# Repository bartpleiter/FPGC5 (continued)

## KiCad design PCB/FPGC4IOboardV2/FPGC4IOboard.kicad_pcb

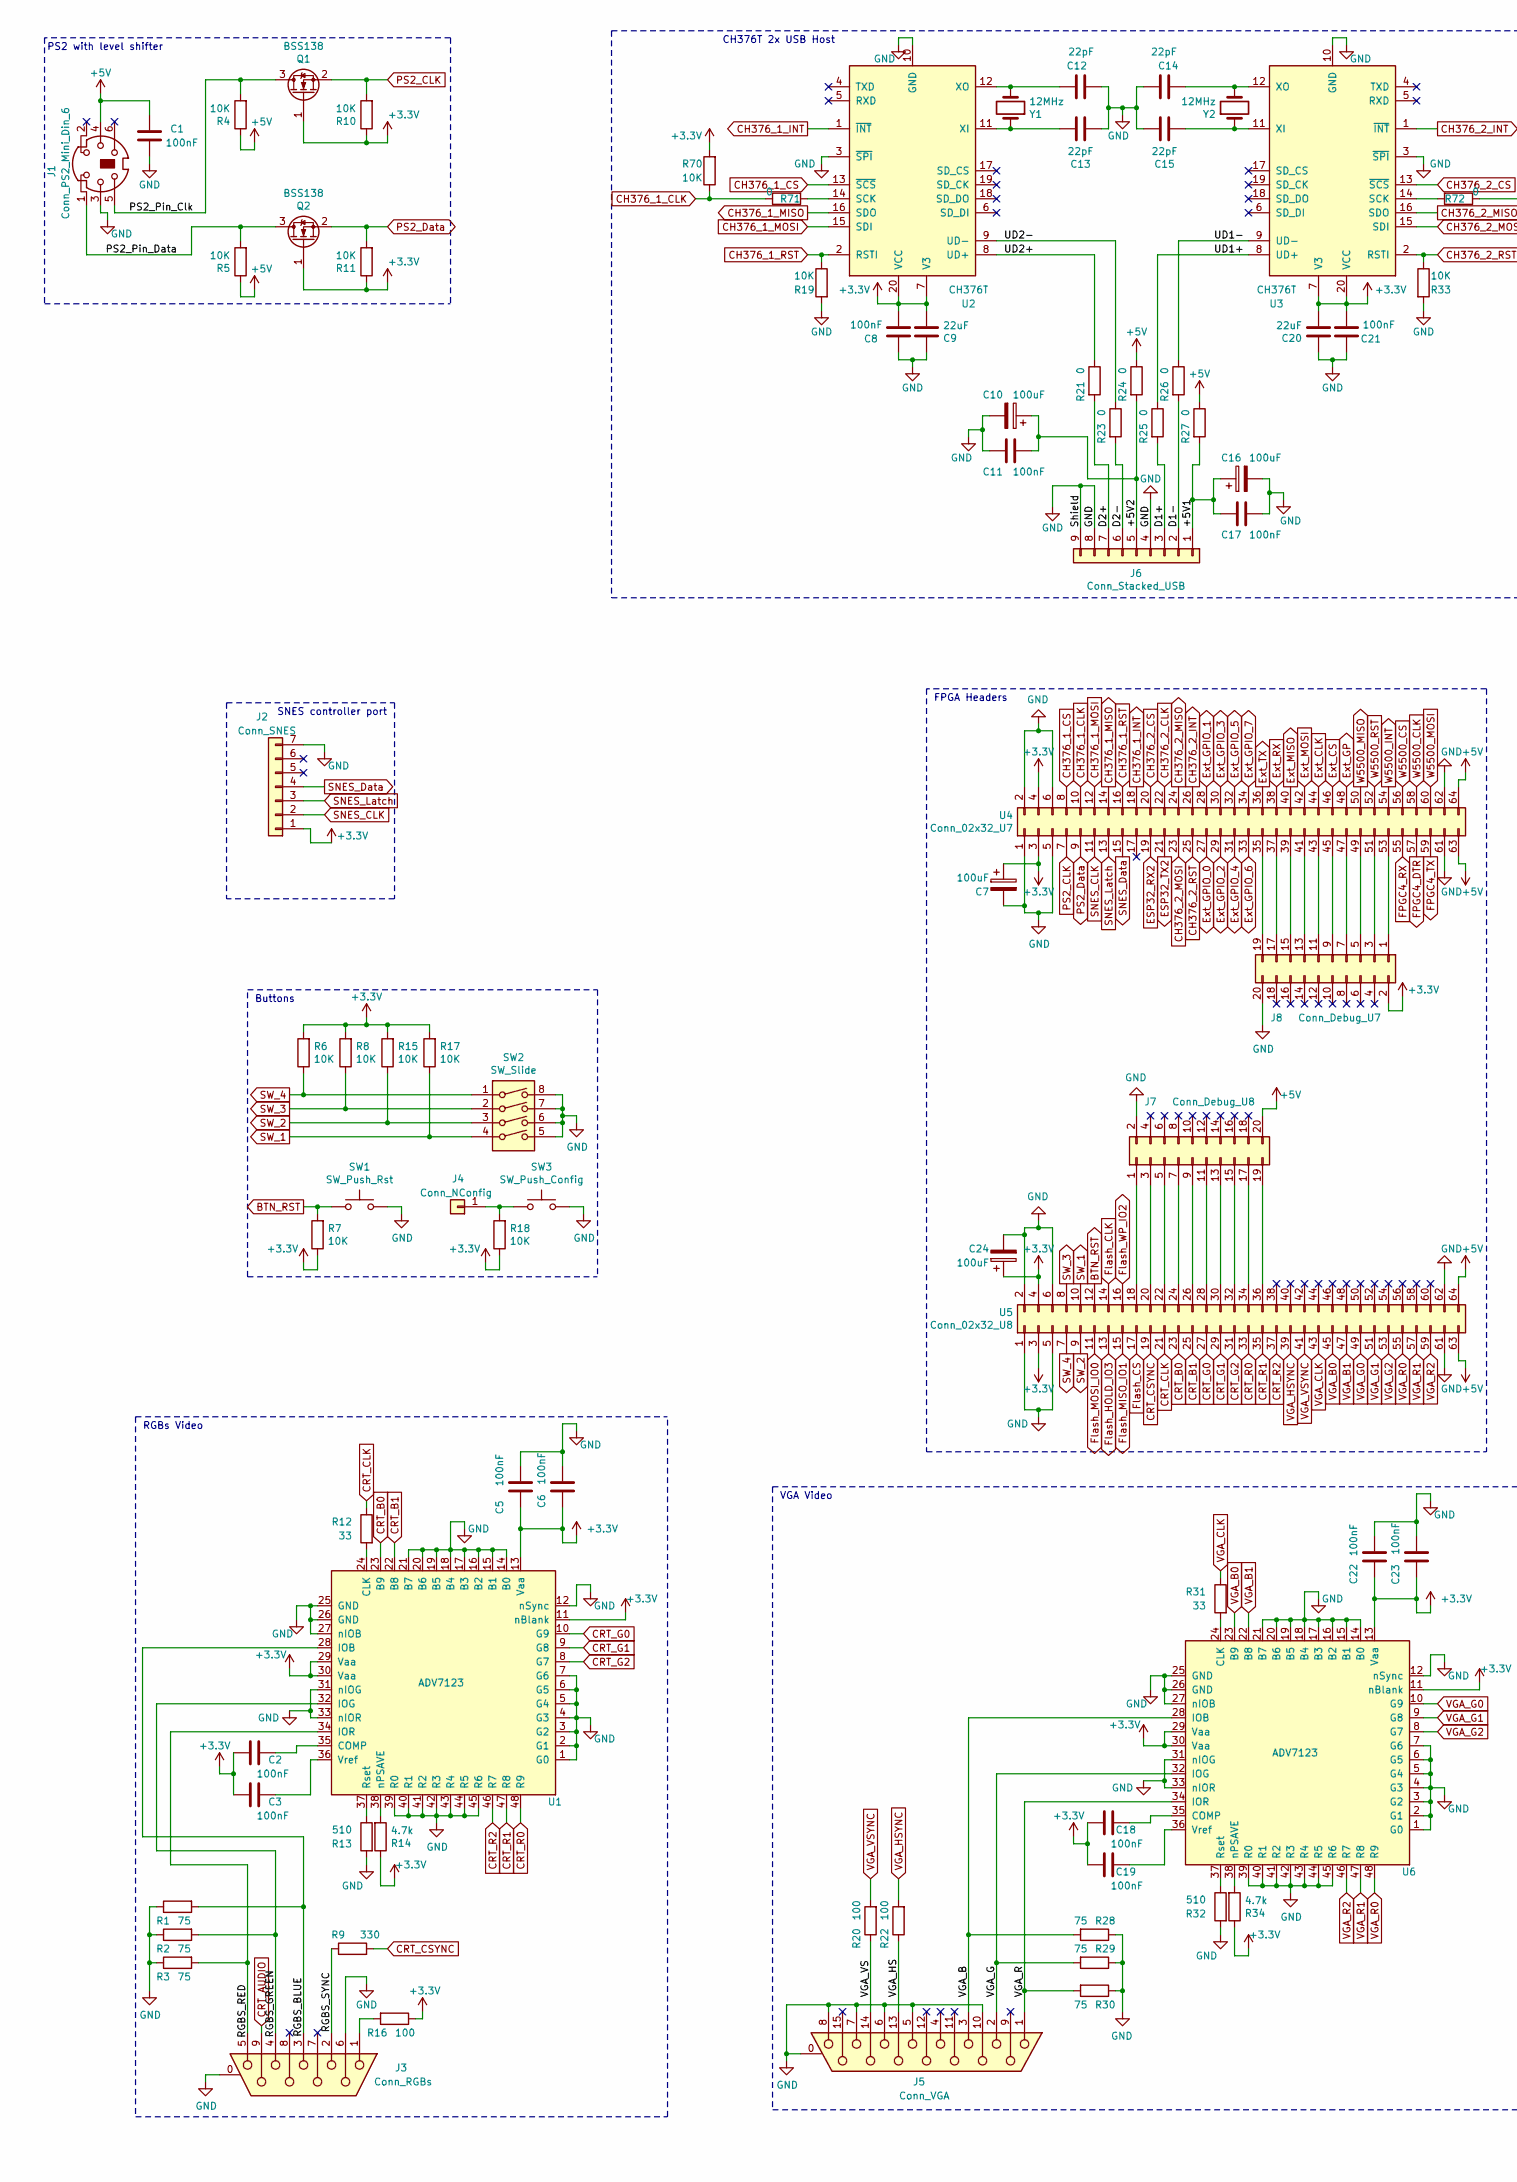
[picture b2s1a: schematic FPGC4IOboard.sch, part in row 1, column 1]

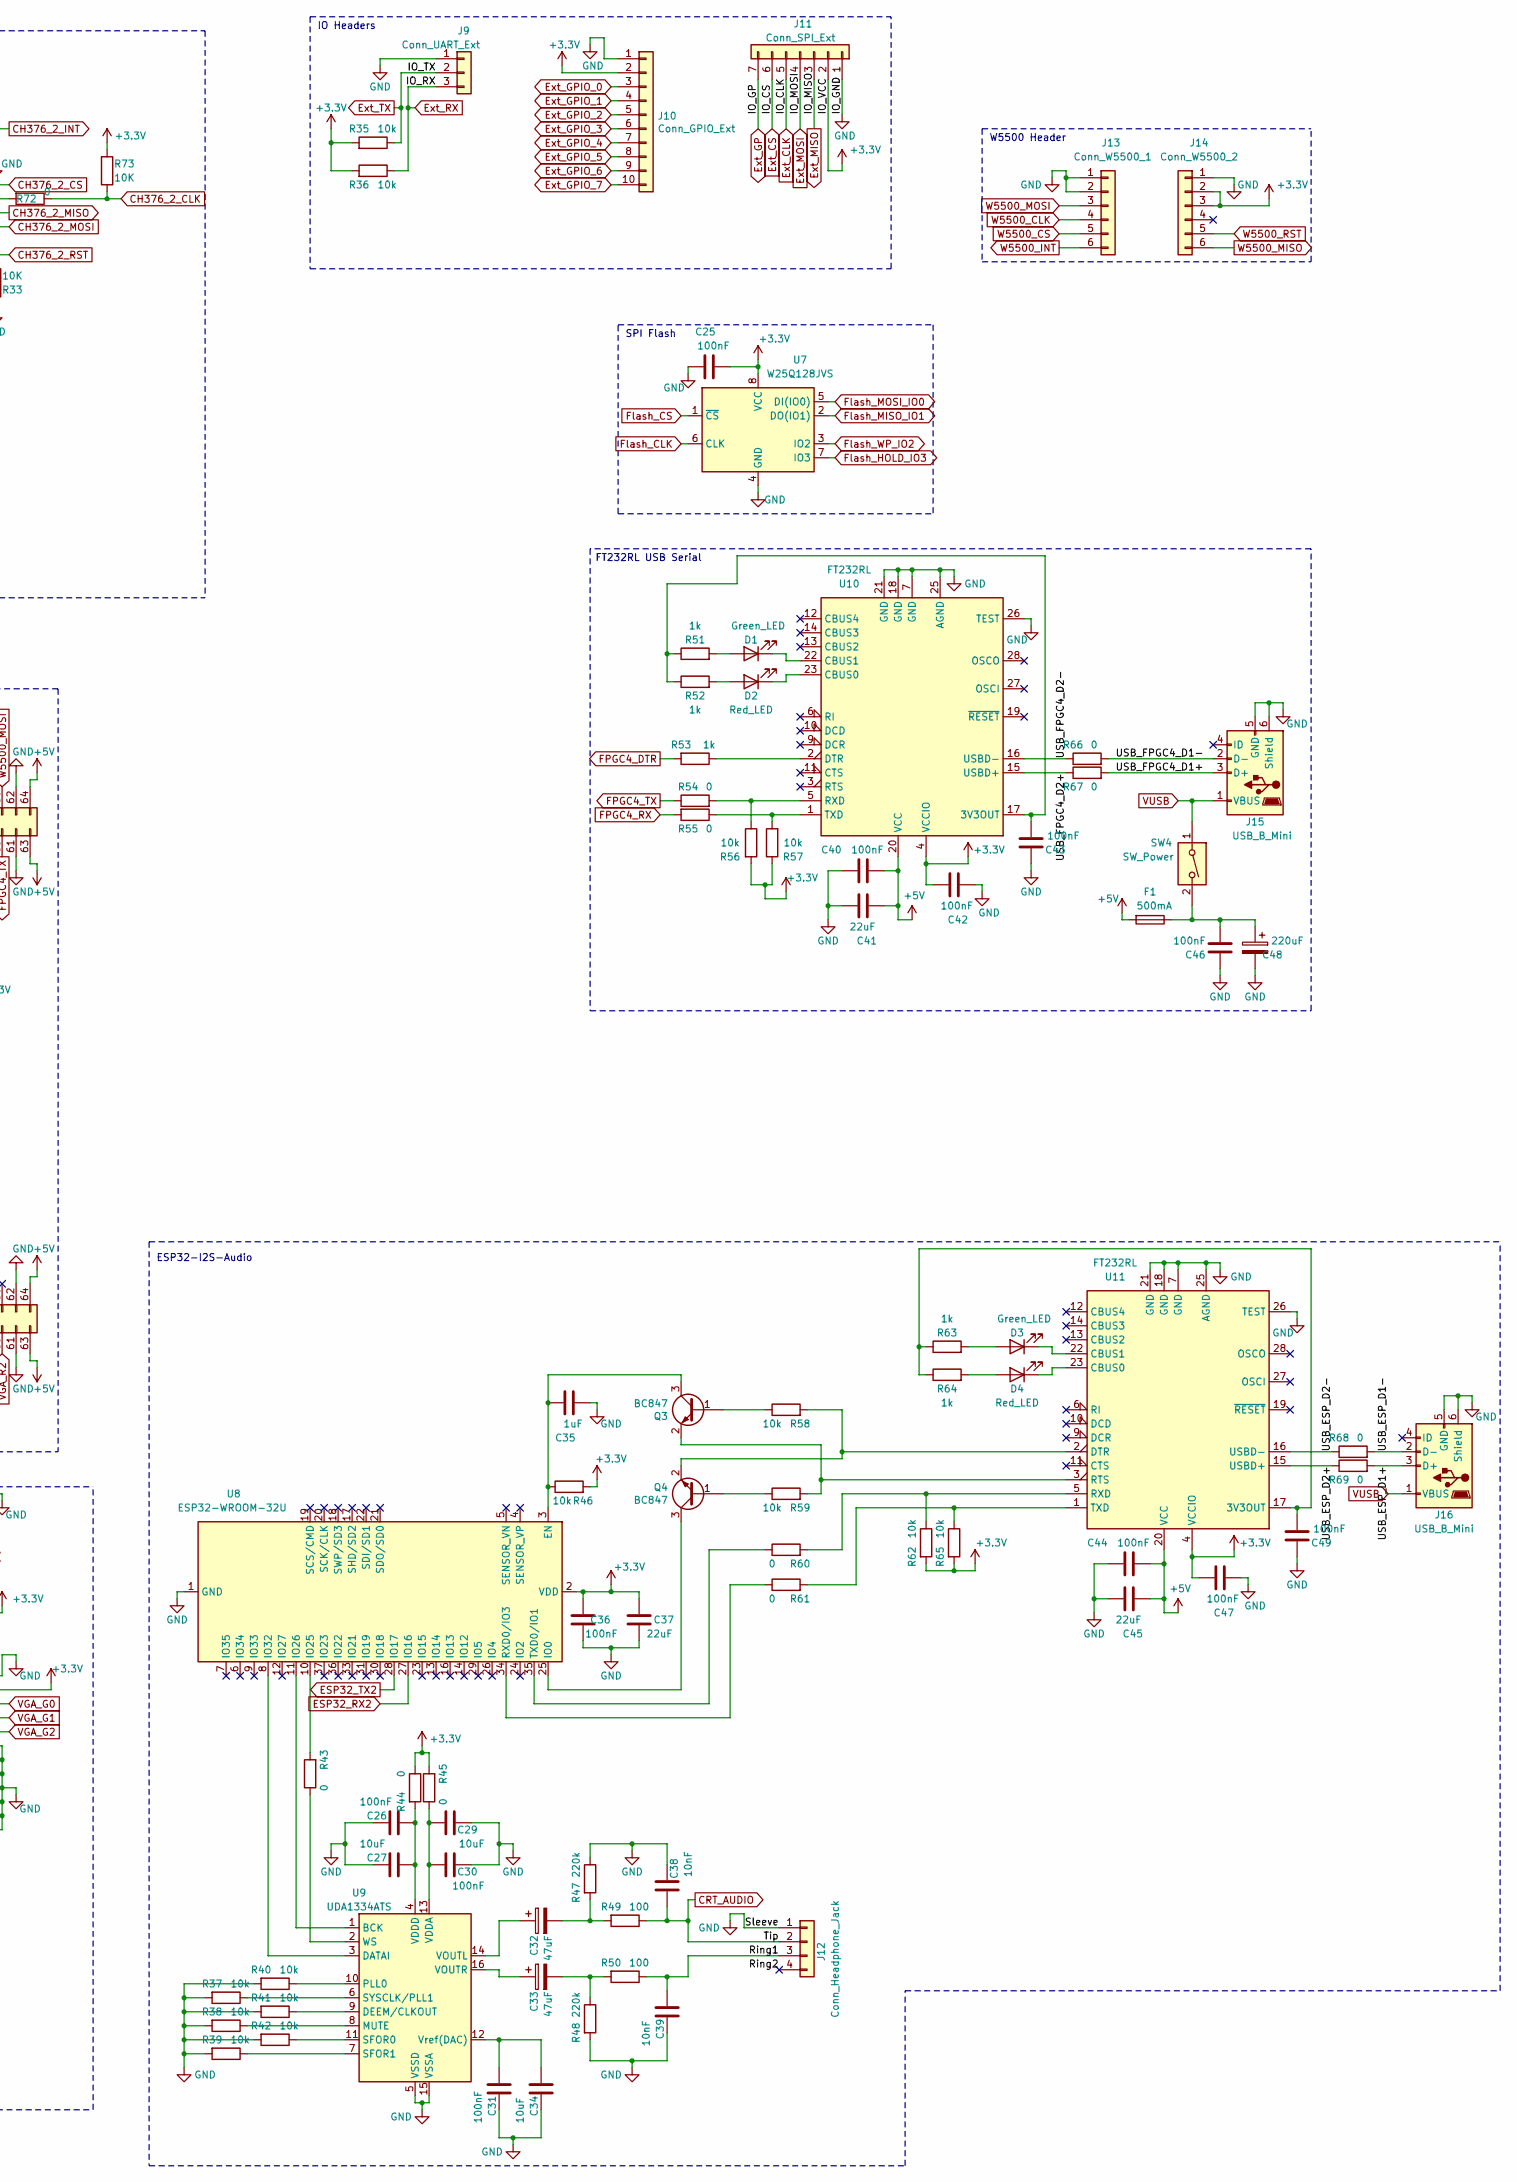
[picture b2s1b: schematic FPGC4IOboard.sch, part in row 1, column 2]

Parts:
C1, C2, C3, C5, C6, C8, C11, C17, C18, C19, C21, C22, C23, C25, C26, C30, C31, C36, C40, C42, C43, C44, C46, C47, C49: 100nF; C_0805_2012Metric_Pad1.15x1.40mm_HandSolder
C7, C10, C16, C24: 100uF; CP_Radial_D4.0mm_P2.00mm
C9, C20, C37, C41, C45: 22uF; C_0805_2012Metric_Pad1.15x1.40mm_HandSolder
C12, C13, C14, C15: 22pF; C_0805_2012Metric_Pad1.15x1.40mm_HandSolder
C27, C29, C34: 10uF; C_0805_2012Metric_Pad1.15x1.40mm_HandSolder
C32, C33: 47uF; CP_Radial_D4.0mm_P2.00mm
C35: 1uF; C_0805_2012Metric_Pad1.15x1.40mm_HandSolder
C38, C39: 10nF; C_0805_2012Metric_Pad1.15x1.40mm_HandSolder
C48: 220uF; CP_Radial_D5.0mm_P2.00mm
D1, D3: Green_LED; LED_0805_2012Metric_Pad1.15x1.40mm_HandSolder
D2, D4: Red_LED; LED_0805_2012Metric_Pad1.15x1.40mm_HandSolder
F1: 500mA; Fuse_1812_4532Metric_Pad1.30x3.40mm_HandSolder
J1: Conn_PS2_Mini_Din_6; Connector_Mini-DIN_Female_6Pin_2rows
J2: Conn_SNES; SNES_controller_port
J3: Conn_RGBs; DSUB9_CRT
J4: Conn_NConfig; PinHeader_1x01_P2.54mm_Vertical
J5: Conn_VGA; VGA_EDAC
J6: Conn_Stacked_USB; USB_A_Wuerth_61400826021_Horizontal_Stacked
J7: Conn_Debug_U8; PinHeader_2x10_P2.54mm_Vertical
J8: Conn_Debug_U7; PinHeader_2x10_P2.54mm_Vertical
J9: Conn_UART_Ext; PinSocket_1x03_P2.54mm_Vertical
J10: Conn_GPIO_Ext; PinSocket_1x10_P2.54mm_Vertical
J11: Conn_SPI_Ext; PinSocket_1x07_P2.54mm_Vertical
J12: Conn_Headphone_Jack; TRRS-PJ-320A
J13: Conn_W5500_1; PinSocket_1x06_P2.54mm_Vertical
J14: Conn_W5500_2; PinSocket_1x06_P2.54mm_Vertical
J15, J16: USB_B_Mini; USB_Mini-B_Lumberg_2486_01_Horizontal
Q1, Q2: BSS138; SOT-23
Q3, Q4: BC847; SOT-23
R1, R2, R3, R28, R29, R30: 75; R_0805_2012Metric_Pad1.15x1.40mm_HandSolder
R4, R5, R6, R7, R8, R10, R11, R15, R17, R18, R19, R33, R70, R73: 10K; R_0805_2012Metric_Pad1.15x1.40mm_HandSolder
R9: 330; R_0805_2012Metric_Pad1.15x1.40mm_HandSolder
R12, R31: 33; R_0805_2012Metric_Pad1.15x1.40mm_HandSolder
R13, R32: 510; R_0805_2012Metric_Pad1.15x1.40mm_HandSolder
R14, R34: 4.7k; R_0805_2012Metric_Pad1.15x1.40mm_HandSolder
R16, R20, R22, R49, R50: 100; R_0805_2012Metric_Pad1.15x1.40mm_HandSolder
R21, R23, R24, R25, R26, R27, R43, R44, R45, R54, R55, R60, R61, R66, R67, R68, R69, R71, R72: 0; R_0805_2012Metric_Pad1.15x1.40mm_HandSolder
R35, R36, R37, R38, R39, R40, R41, R42, R46, R56, R57, R58, R59, R62, R65: 10k; R_0805_2012Metric_Pad1.15x1.40mm_HandSolder
R47, R48: 220k; R_0805_2012Metric_Pad1.15x1.40mm_HandSolder
R51, R52, R53, R63, R64: 1k; R_0805_2012Metric_Pad1.15x1.40mm_HandSolder
SW1: SW_Push_Rst; SW_Tactile_SPST_Angled_PTS645Vx39-2LFS
SW2: SW_Slide; SW_DIP_SPSTx04_Slide_6.7x11.72mm_W8.61mm_P2.54mm_LowProfile
SW3: SW_Push_Config; SW_Tactile_SPST_Angled_PTS645Vx39-2LFS
SW4: SW_Power; switchAngled
U1, U6: ADV7123; LQFP-48_7x7mm_P0.5mm
U2, U3: CH376T; SSOP-20_5.3x7.2mm_P0.65mm
U4: Conn_02x32_U7; PinHeader_2x32_P2.54mm_Vertical
U5: Conn_02x32_U8; PinHeader_2x32_P2.54mm_Vertical
U7: W25Q128JVS; SOIC-8_5.23x5.23mm_P1.27mm
U8: ESP32-WROOM-32U
U9: UDA1334ATS; SSOP-16_4.4x5.2mm_P0.65mm
U10, U11: FT232RL; SSOP-28_5.3x10.2mm_P0.65mm
Y1, Y2: 12MHz; Crystal_HC49-4H_Vertical

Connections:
+3V3: C2.1, C3.1, C5.2, C6.1, C7.1, C8.2, C9.2, C18.1, C19.1, C20.2, C21.2, C22.2, C23.1, C24.1, C25.2, C36.2, C37.2, C42.2, C47.2, J2.1, J8.2, J10.2, J11.2, J14.2, J14.3, Q1.1 (G), Q2.1 (G), R6.2, R7.1, R8.2, R10.1, R11.1, R14.1, R15.2, R16.1, R17.2, R18.1, R34.1, R35.2, R36.2, R44.1, R45.2, R46.2, R56.2, R57.1, R62.2, R65.2, R70.2, R73.2, U1.11 (nBlank), U1.13 (Vaa), U1.29 (Vaa), U1.30 (Vaa), U2.7 (V3), U2.20 (VCC), U3.7 (V3), U3.20 (VCC), U4.3, U4.4, U5.3, U5.4, U6.11 (nBlank), U6.13 (Vaa), U6.29 (Vaa), U6.30 (Vaa), U7.8 (VCC), U8.2 (VDD), U10.4 (VCCIO), U11.4 (VCCIO)
+5V: C1.1, C40.2, C41.1, C44.2, C45.1, F1.2, J1.4, J7.20, R4.1, R5.1, R24.1, R27.1, U4.63, U4.64, U5.63, U5.64, U10.20 (VCC), U11.20 (VCC)
/+5V1: C16.1, C17.2, J6.1, R27.2
/+5V2: C10.1, C11.2, J6.5, R24.2
/D1+: J6.3, R25.2
/D1-: J6.2, R26.2
/D2+: J6.7, R21.2
/D2-: J6.6, R23.2
/PS2_Pin_Clk: J1.5, Q1.3 (D), R4.2
/PS2_Pin_Data: J1.1, Q2.3 (D), R5.2
/RGBS_BLUE: J3.3, R1.2, U1.28 (IOB)
/RGBS_GREEN: J3.4, R2.2, U1.32 (IOG)
/RGBS_RED: J3.5, R3.2, U1.34 (IOR)
/RGBS_SYNC: J3.2, R9.1
/Ring1: C39.1, J12.3, R50.1
/Ring2: J12.4
/UD1+: R25.1, U3.8 (UD+)
/UD1-: R26.1, U3.9 (UD-)
/UD2+: R21.1, U2.8 (UD+)
/UD2-: R23.1, U2.9 (UD-)
/USB_ESP_D1+: J16.3 (D+), R69.2
/USB_ESP_D1-: J16.2 (D-), R68.2
/USB_ESP_D2+: R69.1, U11.15 (USBD+)
/USB_ESP_D2-: R68.1, U11.16 (USBD-)
/USB_FPGC4_D1+: J15.3 (D+), R67.2
/USB_FPGC4_D1-: J15.2 (D-), R66.2
/USB_FPGC4_D2+: R67.1, U10.15 (USBD+)
/USB_FPGC4_D2-: R66.1, U10.16 (USBD-)
/VGA_B: J5.3, R28.2, U6.28 (IOB)
/VGA_G: J5.2, R29.2, U6.32 (IOG)
/VGA_HS: J5.13, R22.1
/VGA_R: J5.1, R30.2, U6.34 (IOR)
/VGA_VS: J5.14, R20.1
BTN_RST: R7.2, SW1.1, U5.12
CH376_1_CLK: R70.1, R71.1, U4.10
CH376_1_CS: U2.13 (~SCS), U4.8
CH376_1_INT: U2.1 (~INT~), U4.18
CH376_1_MISO: U2.16 (SDO), U4.14
CH376_1_MOSI: U2.15 (SDI), U4.12
CH376_1_RST: R19.1, U2.2 (RSTI), U4.16
CH376_2_CLK: R72.1, R73.1, U4.22
CH376_2_CS: U3.13 (~SCS), U4.20
CH376_2_INT: U3.1 (~INT~), U4.26
CH376_2_MISO: U3.16 (SDO), U4.24
CH376_2_MOSI: U3.15 (SDI), U4.23
CH376_2_RST: R33.1, U3.2 (RSTI), U4.25
CRT_AUDIO: C38.1, J3.9, J12.2, R49.1
CRT_B0: U1.23 (B9), U5.23
CRT_B1: U1.22 (B8), U5.25
CRT_CLK: R12.1, U5.21
CRT_CSYNC: R9.2, U5.19
CRT_G0: U1.10 (G9), U5.27
CRT_G1: U1.9 (G8), U5.29
CRT_G2: U1.8 (G7), U5.31
CRT_R0: U1.48 (R9), U5.33
CRT_R1: U1.47 (R8), U5.35
CRT_R2: U1.46 (R7), U5.37
ESP32_RX2: U4.19, U8.27 (IO16)
ESP32_TX2: U4.21, U8.28 (IO17)
Ext_CLK: J11.5, U4.44
Ext_CS: J11.6, U4.46
Ext_GP: J11.7, U4.48
Ext_GPIO_0: J10.3, U4.27
Ext_GPIO_1: J10.4, U4.28
Ext_GPIO_2: J10.5, U4.29
Ext_GPIO_3: J10.6, U4.30
Ext_GPIO_4: J10.7, U4.31
Ext_GPIO_5: J10.8, U4.32
Ext_GPIO_6: J10.9, U4.33
Ext_GPIO_7: J10.10, U4.34
Ext_MISO: J11.3, U4.40
Ext_MOSI: J11.4, U4.42
Ext_RX: J9.3, R36.1, U4.38
Ext_TX: J9.2, R35.1, U4.36
FPGC4_DTR: R53.2, U4.57
FPGC4_RX: R55.2, U4.55
FPGC4_TX: R54.1, U4.59
Flash_CLK: U5.14, U7.6 (CLK)
Flash_CS: U5.17, U7.1 (~CS)
Flash_HOLD_IO3: U5.13, U7.7 (IO3)
Flash_MISO_IO1: U5.15, U7.2 (DO(IO1))
Flash_MOSI_IO0: U5.11, U7.5 (DI(IO0))
Flash_WP_IO2: U5.16, U7.3 (IO2)
GND: C1.2, C5.1, C6.2, C7.2, C8.1, C9.1, C10.2, C11.1, C12.2, C13.1, C14.2, C15.1, C16.2, C17.1, C20.1, C21.1, C22.1, C23.2, C24.2, C25.1, C26.2, C27.2, C29.2, C30.2, C31.2, C34.2, C35.2, C36.1, C37.1, C38.2, C39.2, C40.1, C41.2, C42.1, C43.1, C44.1, C45.2, C46.1, C47.1, C48.2, C49.1, J1.3, J2.7, J3.0 (PAD), J3.6, J5.0 (PAD), J5.5, J5.6, J5.7, J5.8, J5.10, J6.4, J6.8, J6.9, J7.2, J8.20, J9.1, J10.1, J11.1, J12.1, J13.1, J13.2, J14.1, J15.5 (GND), J15.6 (Shield), J16.5 (GND), J16.6 (Shield), R1.1, R2.1, R3.1, R13.2, R19.2, R28.1, R29.1, R30.1, R32.2, R33.2, R37.2, R38.2, R39.2, R40.2, R41.2, R42.2, R47.1, R48.2, SW1.2, SW2.5, SW2.6, SW2.7, SW2.8, SW3.2, U1.1 (G0), U1.2 (G1), U1.3 (G2), U1.4 (G3), U1.5 (G4), U1.6 (G5), U1.7 (G6), U1.12 (nSync), U1.14 (B0), U1.15 (B1), U1.16 (B2), U1.17 (B3), U1.18 (B4), U1.19 (B5), U1.20 (B6), U1.21 (B7), U1.25 (GND), U1.26 (GND), U1.27 (nIOB), U1.31 (nIOG), U1.33 (nIOR), U1.39 (R0), U1.40 (R1), U1.41 (R2), U1.42 (R3), U1.43 (R4), U1.44 (R5), U1.45 (R6), U2.3 (~SPI~), U2.10 (GND), U3.3 (~SPI~), U3.10 (GND), U4.1, U4.2, U4.5, U4.6, U4.61, U4.62, U5.1, U5.2, U5.5, U5.6, U5.61, U5.62, U6.1 (G0), U6.2 (G1), U6.3 (G2), U6.4 (G3), U6.5 (G4), U6.6 (G5), U6.7 (G6), U6.12 (nSync), U6.14 (B0), U6.15 (B1), U6.16 (B2), U6.17 (B3), U6.18 (B4), U6.19 (B5), U6.20 (B6), U6.21 (B7), U6.25 (GND), U6.26 (GND), U6.27 (nIOB), U6.31 (nIOG), U6.33 (nIOR), U6.39 (R0), U6.40 (R1), U6.41 (R2), U6.42 (R3), U6.43 (R4), U6.44 (R5), U6.45 (R6), U7.4 (GND), U8.1 (GND), U8.15 (GND), U8.38 (GND), U8.39 (GND), U9.5 (VSSD), U9.15 (VSSA), U10.7 (GND), U10.18 (GND), U10.21 (GND), U10.25 (AGND), U10.26 (TEST), U11.7 (GND), U11.18 (GND), U11.21 (GND), U11.25 (AGND), U11.26 (TEST)
unnamed: C2.2, U1.35 (COMP)
unnamed: C3.2, U1.36 (Vref)
unnamed: C12.1, U2.12 (XO), Y1.2
unnamed: C13.2, U2.11 (XI), Y1.1
unnamed: C14.1, U3.12 (XO), Y2.2
unnamed: C15.2, U3.11 (XI), Y2.1
unnamed: C18.2, U6.35 (COMP)
unnamed: C19.2, U6.36 (Vref)
unnamed: C26.1, C27.1, R44.2, U9.4 (VDDD)
unnamed: C29.1, C30.1, R45.1, U9.13 (VDDA)
unnamed: C31.1, C34.1, U9.12 (Vref(DAC))
unnamed: C32.1, U9.14 (VOUTL)
unnamed: C32.2, R47.2, R49.2
unnamed: C33.1, U9.16 (VOUTR)
unnamed: C33.2, R48.1, R50.2
unnamed: C35.1, Q3.3 (C), R46.1, U8.3 (EN)
unnamed: C43.2, R51.1, R52.1, U10.17 (3V3OUT)
unnamed: C46.2, C48.1, F1.1, SW4.2
unnamed: C49.2, R63.1, R64.1, U11.17 (3V3OUT)
unnamed: D1.1 (K), U10.22 (CBUS1)
unnamed: D1.2 (A), R51.2
unnamed: D2.1 (K), U10.23 (CBUS0)
unnamed: D2.2 (A), R52.2
unnamed: D3.1 (K), U11.22 (CBUS1)
unnamed: D3.2 (A), R63.2
unnamed: D4.1 (K), U11.23 (CBUS0)
unnamed: D4.2 (A), R64.2
unnamed: J3.1, R16.2
unnamed: J4.1, R18.2, SW3.1
unnamed: J7.1, U5.18
unnamed: J7.3, U5.20
unnamed: J7.5, U5.22
unnamed: J7.7, U5.24
unnamed: J7.9, U5.26
unnamed: J7.11, U5.28
unnamed: J7.13, U5.30
unnamed: J7.15, U5.32
unnamed: J7.17, U5.34
unnamed: J7.19, U5.36
unnamed: J8.1, U4.53
unnamed: J8.3, U4.51
unnamed: J8.5, U4.49
unnamed: J8.7, U4.47
unnamed: J8.9, U4.45
unnamed: J8.11, U4.43
unnamed: J8.13, U4.41
unnamed: J8.15, U4.39
unnamed: J8.17, U4.37
unnamed: J8.19, U4.35
unnamed: Q3.1 (B), R58.1
unnamed: Q3.2 (E), R59.2, U11.3 (RTS)
unnamed: Q4.1 (B), R59.1
unnamed: Q4.2 (E), R58.2, U11.2 (DTR)
unnamed: Q4.3 (C), U8.25 (IO0)
unnamed: R12.2, U1.24 (CLK)
unnamed: R13.1, U1.37 (Rset)
unnamed: R14.2, U1.38 (nPSAVE)
unnamed: R31.2, U6.24 (CLK)
unnamed: R32.1, U6.37 (Rset)
unnamed: R34.2, U6.38 (nPSAVE)
unnamed: R37.1, U9.6 (SYSCLK/PLL1)
unnamed: R38.1, U9.8 (MUTE)
unnamed: R39.1, U9.7 (SFOR1)
unnamed: R40.1, U9.10 (PLL0)
unnamed: R41.1, U9.9 (DEEM/CLKOUT)
unnamed: R42.1, U9.11 (SFOR0)
unnamed: R43.1, U9.2 (WS)
unnamed: R43.2, U8.10 (IO25)
unnamed: R53.1, U10.2 (DTR)
unnamed: R54.2, R56.1, U10.5 (RXD)
unnamed: R55.1, R57.2, U10.1 (TXD)
unnamed: R60.1, U8.35 (TXD0/IO1)
unnamed: R60.2, R62.1, U11.5 (RXD)
unnamed: R61.1, U8.34 (RXD0/IO3)
unnamed: R61.2, R65.1, U11.1 (TXD)
unnamed: R71.2, U2.14 (SCK)
unnamed: R72.2, U3.14 (SCK)
unnamed: U8.8 (IO32), U9.3 (DATAI)
unnamed: U8.11 (IO26), U9.1 (BCK)
PS2_CLK: Q1.2 (S), R10.2, U4.7
PS2_Data: Q2.2 (S), R11.2, U4.9
SNES_CLK: J2.2, U4.11
SNES_Data: J2.4, U4.15
SNES_Latch: J2.3, U4.13
SW_1: R17.1, SW2.4, U5.10
SW_2: R15.1, SW2.3, U5.9
SW_3: R8.1, SW2.2, U5.8
SW_4: R6.1, SW2.1, U5.7
VGA_B0: U5.45, U6.23 (B9)
VGA_B1: U5.47, U6.22 (B8)
VGA_CLK: R31.1, U5.43
VGA_G0: U5.49, U6.10 (G9)
VGA_G1: U5.51, U6.9 (G8)
VGA_G2: U5.53, U6.8 (G7)
VGA_HSYNC: R22.2, U5.39
VGA_R0: U5.55, U6.48 (R9)
VGA_R1: U5.57, U6.47 (R8)
VGA_R2: U5.59, U6.46 (R7)
VGA_VSYNC: R20.2, U5.41
VUSB: J15.1 (VBUS), J16.1 (VBUS), SW4.1
W5500_CLK: J13.4, U4.58
W5500_CS: J13.5, U4.56
W5500_INT: J13.6, U4.54
W5500_MISO: J14.6, U4.50
W5500_MOSI: J13.3, U4.60
W5500_RST: J14.5, U4.52

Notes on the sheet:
FT232RL USB Serial
IO Headers
SNES controller port
PS2 with level shifter
CH376T 2x USB Host
RGBs Video
VGA Video
ESP32-I2S-Audio
SPI Flash
W5500 Header
Buttons
FPGA Headers

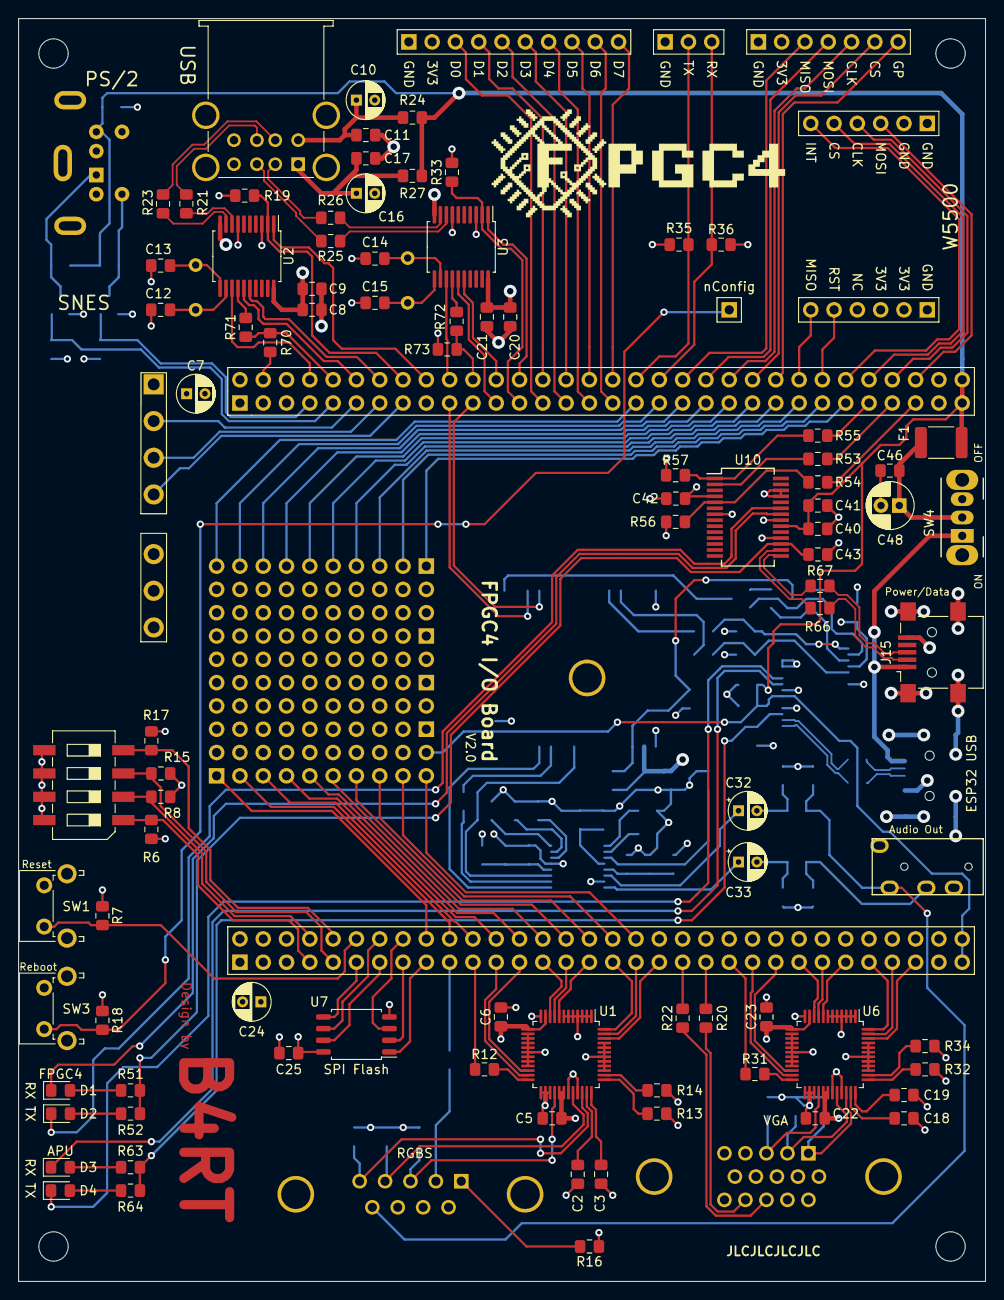
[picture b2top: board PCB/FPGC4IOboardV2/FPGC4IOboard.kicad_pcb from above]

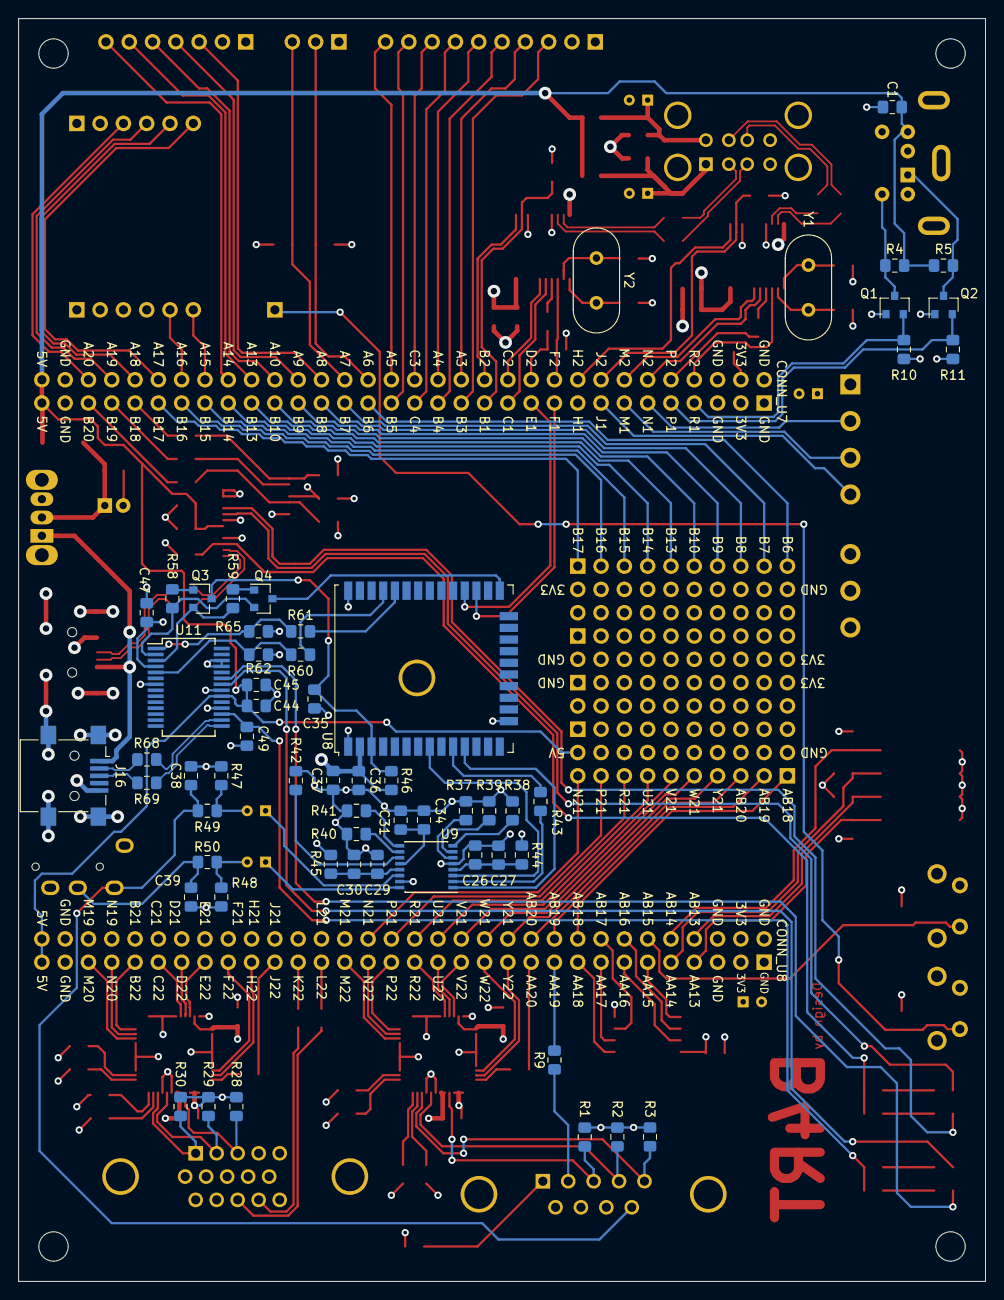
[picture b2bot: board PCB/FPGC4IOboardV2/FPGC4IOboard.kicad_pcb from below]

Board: 4 copper layers, 105.4 x 137.7 mm, 163 parts (59 on the bottom side), 189 nets.

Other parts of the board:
LOGO: LOGO

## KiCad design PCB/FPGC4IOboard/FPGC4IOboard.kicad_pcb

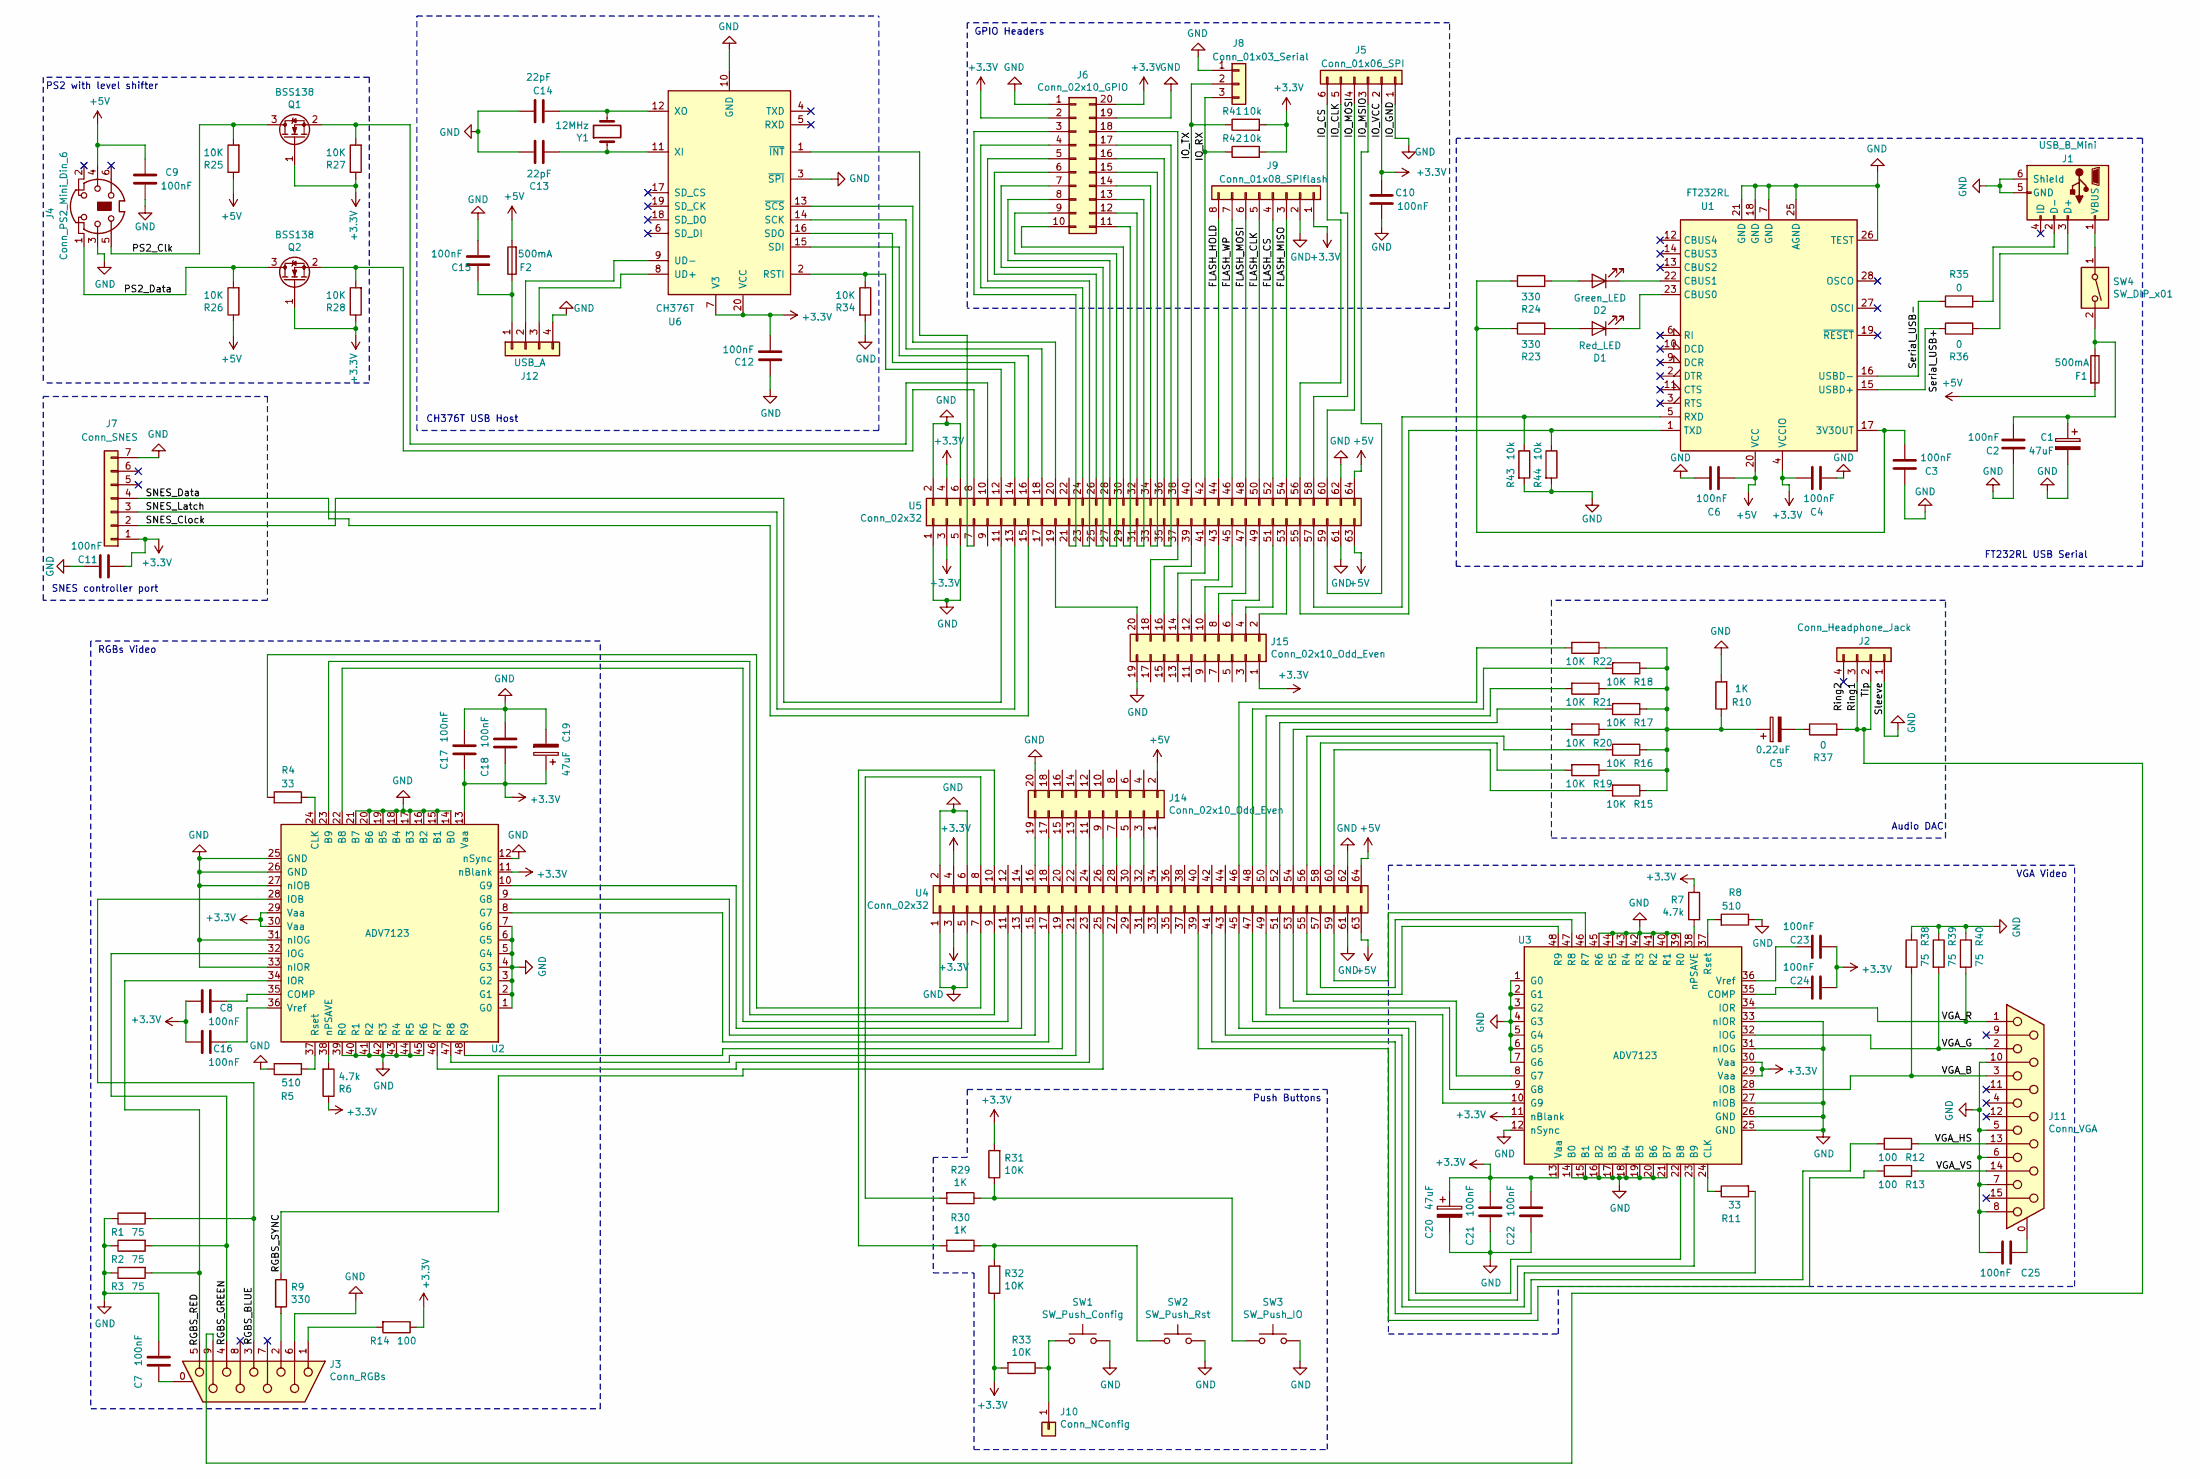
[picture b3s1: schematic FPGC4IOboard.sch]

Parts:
C1, C19, C20: 47uF; CP_Radial_D6.3mm_P2.50mm
C2, C3, C4, C6, C7, C8, C9, C10, C11, C12, C15, C16, C17, C18, C21, C22, C23, C24, C25: 100nF; C_0805_2012Metric_Pad1.15x1.40mm_HandSolder
C5: 0.22uF; CP_Radial_D6.3mm_P2.50mm
C13, C14: 22pF; C_0805_2012Metric_Pad1.15x1.40mm_HandSolder
D1: Red_LED; LED_0805_2012Metric_Pad1.15x1.40mm_HandSolder
D2: Green_LED; LED_0805_2012Metric_Pad1.15x1.40mm_HandSolder
F1, F2: 500mA; Fuse_1812_4532Metric_Pad1.30x3.40mm_HandSolder
J1: USB_B_Mini; USB_Mini-B_Lumberg_2486_01_Horizontal
J2: Conn_Headphone_Jack; TRRS-PJ-320A
J3: Conn_RGBs; DSUB-9
J4: Conn_PS2_Mini_Din_6; Connector_Mini-DIN_Female_6Pin_2rows
J5: Conn_01x06_SPI; PinSocket_1x06_P2.54mm_Vertical
J6: Conn_02x10_GPIO; PinHeader_2x10_P2.54mm_Vertical
J7: Conn_SNES; SNES_controller_port
J8: Conn_01x03_Serial; PinSocket_1x03_P2.54mm_Vertical
J9: Conn_01x08_SPIflash; PinSocket_1x08_P2.54mm_Vertical
J10: Conn_NConfig; PinHeader_1x01_P2.54mm_Vertical
J11: Conn_VGA; DSUB-15-HD_Female_Horizontal_P2.29x1.98mm_EdgePinOffset8.35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
J12: USB_A; conn_usb_A
J14, J15: Conn_02x10_Odd_Even; debugSocket2x10
Q1, Q2: BSS138; SOT-23
R1, R2, R3, R38, R39, R40: 75; R_0805_2012Metric_Pad1.15x1.40mm_HandSolder
R4, R11: 33; R_0805_2012Metric_Pad1.15x1.40mm_HandSolder
R5, R8: 510; R_0805_2012Metric_Pad1.15x1.40mm_HandSolder
R6, R7: 4.7k; R_0805_2012Metric_Pad1.15x1.40mm_HandSolder
R9, R23, R24: 330; R_0805_2012Metric_Pad1.15x1.40mm_HandSolder
R10, R29, R30: 1K; R_0805_2012Metric_Pad1.15x1.40mm_HandSolder
R12, R13, R14: 100; R_0805_2012Metric_Pad1.15x1.40mm_HandSolder
R15, R16, R17, R18, R19, R20, R21, R22, R25, R26, R27, R28, R31, R32, R33, R34: 10K; R_0805_2012Metric_Pad1.15x1.40mm_HandSolder
R35, R36, R37: 0; R_0805_2012Metric_Pad1.15x1.40mm_HandSolder
R41, R42, R43, R44: 10k; R_0805_2012Metric_Pad1.15x1.40mm_HandSolder
SW1: SW_Push_Config; SW_Tactile_SPST_Angled_PTS645Vx39-2LFS
SW2: SW_Push_Rst; SW_Tactile_SPST_Angled_PTS645Vx39-2LFS
SW3: SW_Push_IO; SW_Tactile_SPST_Angled_PTS645Vx39-2LFS
SW4: SW_DIP_x01; switchAngled
U1: FT232RL; SSOP-28_5.3x10.2mm_P0.65mm
U2, U3: ADV7123; LQFP-48_7x7mm_P0.5mm
U4, U5: Conn_02x32; PinHeader_2x32_P2.54mm_Vertical
U6: CH376T; SSOP-20_5.3x7.2mm_P0.65mm
Y1: 12MHz; Crystal_HC49-4H_Vertical

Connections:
+3V3: C4.2, C8.1, C10.1, C11.1, C12.2, C16.1, C17.2, C18.1, C19.1, C20.1, C21.2, C22.2, C23.1, C24.1, J5.2, J6.2, J6.20, J7.1, J9.1, J15.1, Q1.1 (G), Q2.1 (G), R6.1, R7.1, R14.1, R27.1, R28.1, R31.2, R32.1, R33.2, R41.2, R42.2, U1.4 (VCCIO), U2.11 (nBlank), U2.13 (Vaa), U2.29 (Vaa), U2.30 (Vaa), U3.11 (nBlank), U3.13 (Vaa), U3.29 (Vaa), U3.30 (Vaa), U4.3, U4.4, U5.3, U5.4, U6.7 (V3), U6.20 (VCC)
+5V: C6.2, C9.1, F1.2, F2.2, J4.4, J14.2, R25.1, R26.1, U1.20 (VCC), U4.63, U4.64, U5.63, U5.64
/FLASH_CLK: J9.5, U5.50
/FLASH_CS: J9.4, U5.52
/FLASH_HOLD: J9.8, U5.44
/FLASH_MISO: J9.3, U5.54
/FLASH_MOSI: J9.6, U5.48
/FLASH_WP: J9.7, U5.46
/IO_CLK: J5.5, U5.58
/IO_CS: J5.6, U5.56
/IO_MOSI: J5.4, U5.60
/IO_MSIO: J5.3, U5.59
/IO_RX: J8.3, R42.1, U5.42
/IO_TX: J8.2, R41.1, U5.40
/PS2_Clk: J4.5, Q1.3 (D), R25.2
/PS2_Data: J4.1, Q2.3 (D), R26.2
/RGBS_BLUE: J3.3, R1.2, U2.28 (IOB)
/RGBS_GREEN: J3.4, R2.2, U2.32 (IOG)
/RGBS_RED: J3.5, R3.2, U2.34 (IOR)
/RGBS_SYNC: R9.1, U4.25
/Ring1: J2.2, J2.3, J3.9, R37.2
/Ring2: J2.4
/SNES_Clock: J7.2, U5.11
/SNES_Data: J7.4, U5.15
/SNES_Latch: J7.3, U5.13
/Serial_USB+: R36.1, U1.15 (USBD+)
/Serial_USB-: R35.1, U1.16 (USBD-)
/VGA_B: J11.3, R38.2, U3.28 (IOB)
/VGA_G: J11.2, R39.2, U3.32 (IOG)
/VGA_HS: J11.13, R12.1
/VGA_R: J11.1, R40.2, U3.34 (IOR)
/VGA_VS: J11.14, R13.1
GND: C1.2, C2.1, C3.1, C4.1, C6.1, C7.2, C9.2, C10.2, C11.2, C12.1, C13.1, C14.2, C15.2, C17.1, C18.2, C19.2, C20.2, C21.1, C22.1, C25.2, J1.5 (GND), J1.6 (Shield), J2.1, J3.6, J4.3, J5.1, J6.1, J6.19, J7.7, J8.1, J9.2, J11.5, J11.6, J11.7, J11.8, J11.10, J12.4, J14.20, J15.19, R1.1, R2.1, R3.1, R5.1, R8.1, R10.2, R34.2, R38.1, R39.1, R40.1, R43.2, R44.2, SW1.2, SW2.2, SW3.2, U1.7 (GND), U1.18 (GND), U1.21 (GND), U1.25 (AGND), U1.26 (TEST), U2.1 (G0), U2.2 (G1), U2.3 (G2), U2.4 (G3), U2.5 (G4), U2.6 (G5), U2.7 (G6), U2.12 (nSync), U2.14 (B0), U2.15 (B1), U2.16 (B2), U2.17 (B3), U2.18 (B4), U2.19 (B5), U2.20 (B6), U2.21 (B7), U2.25 (GND), U2.26 (GND), U2.27 (nIOB), U2.31 (nIOG), U2.33 (nIOR), U2.39 (R0), U2.40 (R1), U2.41 (R2), U2.42 (R3), U2.43 (R4), U2.44 (R5), U2.45 (R6), U3.1 (G0), U3.2 (G1), U3.3 (G2), U3.4 (G3), U3.5 (G4), U3.6 (G5), U3.7 (G6), U3.12 (nSync), U3.14 (B0), U3.15 (B1), U3.16 (B2), U3.17 (B3), U3.18 (B4), U3.19 (B5), U3.20 (B6), U3.21 (B7), U3.25 (GND), U3.26 (GND), U3.27 (nIOB), U3.31 (nIOG), U3.33 (nIOR), U3.39 (R0), U3.40 (R1), U3.41 (R2), U3.42 (R3), U3.43 (R4), U3.44 (R5), U3.45 (R6), U4.1, U4.2, U4.5, U4.6, U4.61, U4.62, U5.1, U5.2, U5.5, U5.6, U5.61, U5.62, U6.3 (~SPI~), U6.10 (GND)
unnamed: C1.1, C2.2, F1.1, SW4.2
unnamed: C3.2, R23.1, R24.1, U1.17 (3V3OUT)
unnamed: C5.1, R10.1, R15.1, R16.1, R17.1, R18.1, R19.1, R20.1, R21.1, R22.1
unnamed: C5.2, R37.1
unnamed: C7.1, J3.0 (PAD)
unnamed: C8.2, U2.35 (COMP)
unnamed: C13.2, U6.11 (XI), Y1.1
unnamed: C14.1, U6.12 (XO), Y1.2
unnamed: C15.1, F2.1, J12.1
unnamed: C16.2, U2.36 (Vref)
unnamed: C23.2, U3.36 (Vref)
unnamed: C24.2, U3.35 (COMP)
unnamed: C25.1, J11.0 (PAD)
unnamed: D1.1 (K), U1.23 (CBUS0)
unnamed: D1.2 (A), R23.2
unnamed: D2.1 (K), U1.22 (CBUS1)
unnamed: D2.2 (A), R24.2
unnamed: J1.1 (VBUS), SW4.1
unnamed: J1.2 (D-), R35.2
unnamed: J1.3 (D+), R36.2
unnamed: J3.1, R14.2
unnamed: J3.2, R9.2
unnamed: J6.3, U5.21
unnamed: J6.4, U5.24
unnamed: J6.5, U5.23
unnamed: J6.6, U5.26
unnamed: J6.7, U5.25
unnamed: J6.8, U5.28
unnamed: J6.9, U5.27
unnamed: J6.10, U5.30
unnamed: J6.11, U5.29
unnamed: J6.12, U5.32
unnamed: J6.13, U5.31
unnamed: J6.14, U5.34
unnamed: J6.15, U5.33
unnamed: J6.16, U5.36
unnamed: J6.17, U5.35
unnamed: J6.18, U5.38
unnamed: J10.1, R33.1, SW1.1
unnamed: J12.2, U6.9 (UD-)
unnamed: J12.3, U6.8 (UD+)
unnamed: J14.1, U4.34
unnamed: J14.3, U4.32
unnamed: J14.5, U4.30
unnamed: J14.7, U4.28
unnamed: J14.9, U4.26
unnamed: J14.11, U4.24
unnamed: J14.13, U4.22
unnamed: J14.15, U4.20
unnamed: J14.17, U4.18
unnamed: J14.19, U4.16
unnamed: J15.2, U5.53
unnamed: J15.4, U5.51
unnamed: J15.6, U5.49
unnamed: J15.8, U5.47
unnamed: J15.10, U5.45
unnamed: J15.12, U5.43
unnamed: J15.14, U5.41
unnamed: J15.16, U5.39
unnamed: J15.18, U5.37
unnamed: J15.20, U5.19
unnamed: Q1.2 (S), R27.2, U5.10
unnamed: Q2.2 (S), R28.2, U5.8
unnamed: R4.1, U2.24 (CLK)
unnamed: R4.2, U4.7
unnamed: R5.2, U2.37 (Rset)
unnamed: R6.2, U2.38 (nPSAVE)
unnamed: R7.2, U3.38 (nPSAVE)
unnamed: R8.2, U3.37 (Rset)
unnamed: R11.1, U3.24 (CLK)
unnamed: R11.2, U4.43
unnamed: R12.2, U4.41
unnamed: R13.2, U4.39
unnamed: R15.2, U4.60
unnamed: R16.2, U4.56
unnamed: R17.2, U4.52
unnamed: R18.2, U4.48
unnamed: R19.2, U4.58
unnamed: R20.2, U4.54
unnamed: R21.2, U4.50
unnamed: R22.2, U4.46
unnamed: R29.1, R31.1, SW3.1
unnamed: R29.2, U4.8
unnamed: R30.1, R32.2, SW2.1
unnamed: R30.2, U4.10
unnamed: R34.1, U5.12, U6.2 (RSTI)
unnamed: R43.1, U1.5 (RXD), U5.57
unnamed: R44.1, U1.1 (TXD), U5.55
unnamed: U2.8 (G7), U4.17
unnamed: U2.9 (G8), U4.15
unnamed: U2.10 (G9), U4.13
unnamed: U2.22 (B8), U4.11
unnamed: U2.23 (B9), U4.9
unnamed: U2.46 (R7), U4.23
unnamed: U2.47 (R8), U4.21
unnamed: U2.48 (R9), U4.19
unnamed: U3.8 (G7), U4.53
unnamed: U3.9 (G8), U4.51
unnamed: U3.10 (G9), U4.49
unnamed: U3.22 (B8), U4.47
unnamed: U3.23 (B9), U4.45
unnamed: U3.46 (R7), U4.59
unnamed: U3.47 (R8), U4.57
unnamed: U3.48 (R9), U4.55
unnamed: U5.7, U6.1 (~INT~)
unnamed: U5.14, U6.16 (SDO)
unnamed: U5.16, U6.15 (SDI)
unnamed: U5.18, U6.14 (SCK)
unnamed: U5.20, U6.13 (~SCS)

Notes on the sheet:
Audio DAC
FT232RL USB Serial
Push Buttons
GPIO Headers
SNES controller port
PS2 with level shifter
CH376T USB Host
RGBs Video
VGA Video
